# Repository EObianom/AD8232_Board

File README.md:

# AD8232_Board
AD8232 Mini ECG Breakout Board

A compact, production-ready ECG front-end built around the AD8232, designed for seamless integration into wearable and embedded systems.

Small in size, deliberate in design, and ready to manufacture.

## Overview

This project implements a highly miniaturised ECG acquisition circuit with a footprint of just 25mm × 17.7mm. It is engineered for space-constrained applications where traditional breakout boards fall short. Unlike conventional AD8232 modules, this design eliminates the bulky 3.5mm audio jack, enabling direct electrode interfacing and tighter system integration. The result is a clean, flexible, and deployment-ready biosignal front-end.

## Features
- Ultra-compact PCB (25mm × 17.7mm)
- Based on the AD8232 analog front-end for ECG signal conditioning
- Direct electrode interface (no audio jack) for reduced size and flexibility
- Carefully designed layout for low-noise signal acquisition
- Manufacturing-ready with full fabrication and assembly files

## Repository Contents
This repository provides a complete, production-ready hardware package:
1. Schematic
2. PCB Layout: Optimised layout focused on compactness.
3. Footprints: All components mapped to manufacturable, assembly-ready footprints.
4. Gerber Files: Fabrication files ready for immediate PCB manufacturing.
5. BOM (JLC Format): Bill of Materials.
6. CPL File: Pick-and-place file for automated component assembly.

## Getting Started

1. Review the schematic to understand the circuit design
2. Open the PCB layout in KiCad to inspect routing and placement
3. Use the Gerber files to order your PCB
4. Upload the BOM and CPL files to JLCPCB (or similar) for assembly

Once assembled, the board can be interfaced with a microcontroller ADC for signal capture and processing.

## Applications

- Wearable health monitoring devices
- Embedded ECG systems
- Biomedical research prototypes
- Low-power biosignal acquisition platforms

---

Disclaimer
This design is intended for research and development purposes only. It is not certified for medical or clinical use. This work is licensed under a Creative Commons Attribution-NonCommercial 4.0 International License.

Contributions and improvements are welcome.
Feel free to open an issue or submit a pull request.

Designed and developed by Ekenedirichukwu Obianom.

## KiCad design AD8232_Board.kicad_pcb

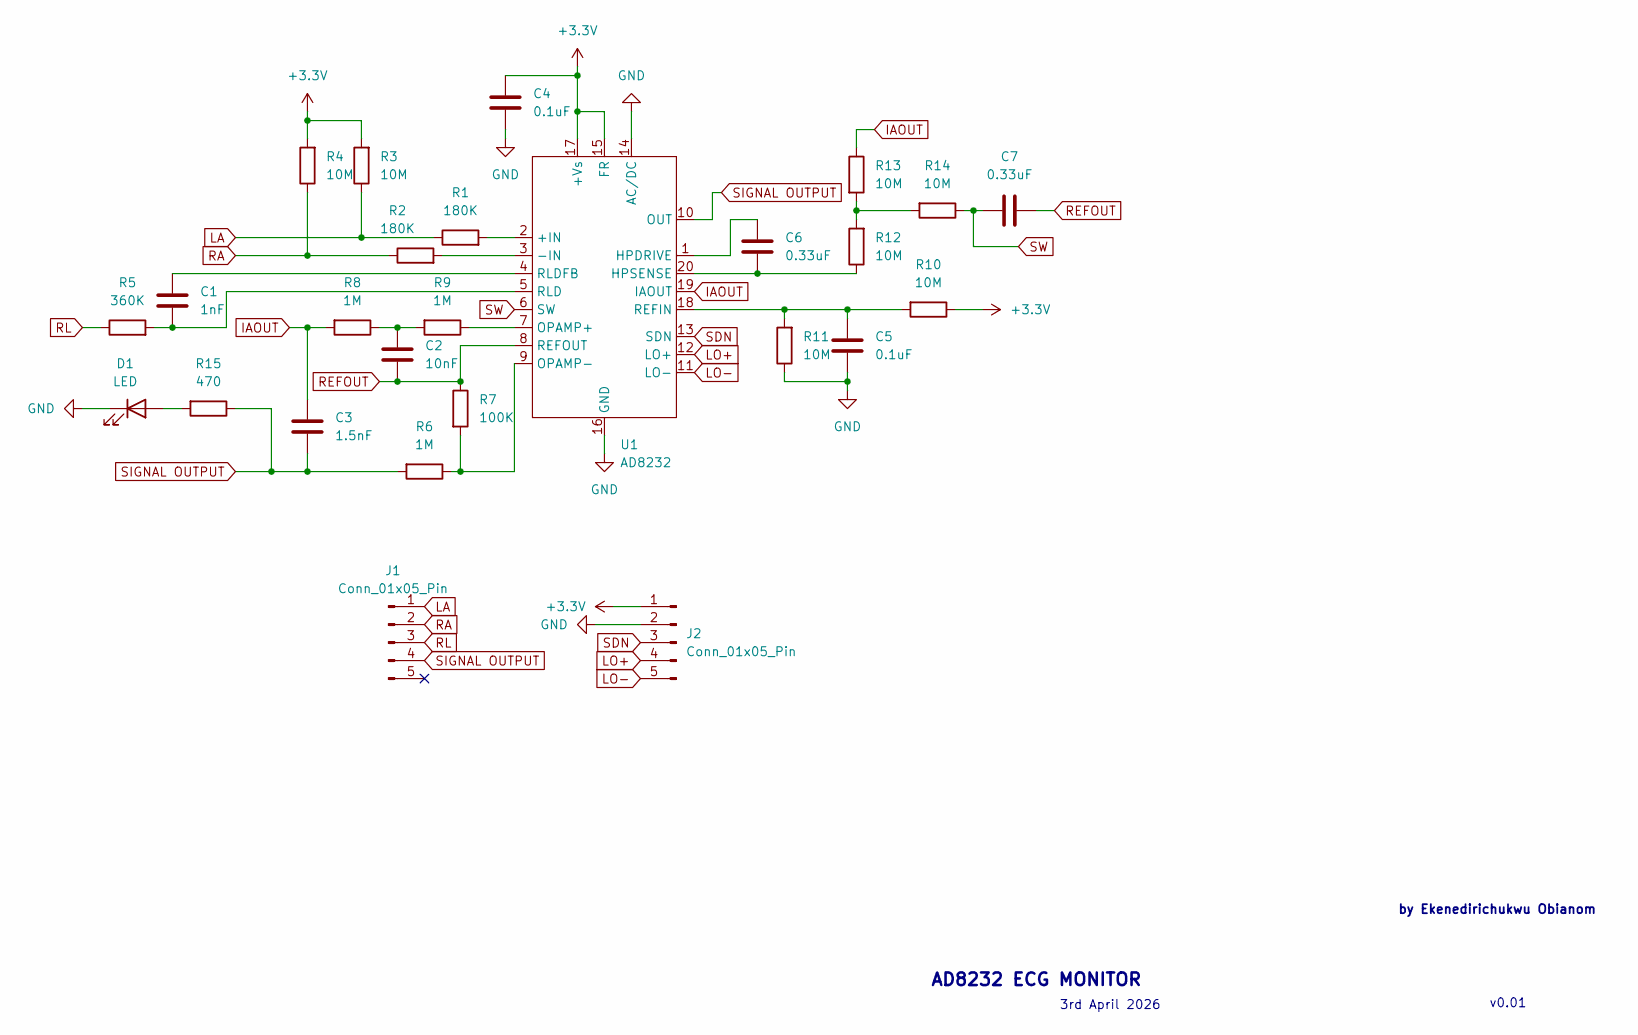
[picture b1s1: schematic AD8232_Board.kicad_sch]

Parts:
C1: 1nF; C_0603_1608Metric
C2: 10nF; C_0603_1608Metric
C3: 1.5nF; C_0603_1608Metric
C4, C5: 0.1uF; C_0603_1608Metric
C6, C7: 0.33uF; C_0603_1608Metric
D1: LED; LED_0603_1608Metric
J1, J2: Conn_01x05_Pin; PinHeader_1x05_P2.54mm_Vertical
R1, R2: 180K; R_0805_2012Metric
R3, R4, R10, R11, R12, R13, R14: 10M; R_0603_1608Metric
R5: 360K; R_1206_3216Metric
R6, R8, R9: 1M; R_0805_2012Metric
R7: 100K; R_0603_1608Metric
R15: 470; R_0805_2012Metric
U1: AD8232; QFN-20-1EP_4x4mm_P0.5mm_EP2.6x2.6mm

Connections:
+3.3V: C4.1, J2.1, R3.2, R4.2, R10.1, U1.15 (FR), U1.17 (+Vs)
GND: C4.2, C5.2, D1.1 (K), J2.2, R11.1, U1.14 (AC/DC), U1.16 (GND), U1.21 (GND)
IAOUT: C3.1, R8.2, R13.1, U1.19 (IAOUT)
LA: J1.1, R1.1, R3.1
LO+: J2.4, U1.12 (LO+)
LO-: J2.5, U1.11 (LO-)
unnamed: C2.1, R8.1, R9.2
unnamed: D1.2 (A), R15.2
unnamed: R12.2, R13.2, R14.2
unnamed: R1.2, U1.2 (+IN)
unnamed: R2.2, U1.3 (-IN)
unnamed: C6.1, U1.1 (HPDRIVE)
unnamed: C6.2, R12.1, U1.20 (HPSENSE)
unnamed: R9.1, U1.7 (OPAMP+)
unnamed: R6.1, R7.2, U1.9 (OPAMP-)
unnamed: C5.1, R10.2, R11.2, U1.18 (REFIN)
unnamed: C1.2, R5.2, U1.5 (RLD)
unnamed: C1.1, U1.4 (RLDFB)
RA: J1.2, R2.1, R4.1
REFOUT: C2.2, C7.2, R7.1, U1.8 (REFOUT)
RL: J1.3, R5.1
SDN: J2.3, U1.13 (SDN)
SIGNAL OUTPUT: C3.2, J1.4, R6.2, R15.1, U1.10 (OUT)
SW: C7.1, R14.1, U1.6 (SW)

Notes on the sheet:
by Ekenedirichukwu Obianom
3rd April 2026
v0.01
AD8232 ECG MONITOR

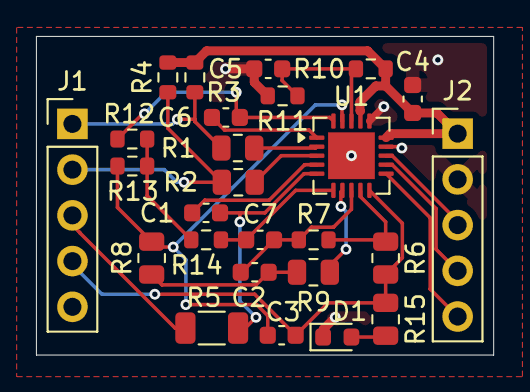
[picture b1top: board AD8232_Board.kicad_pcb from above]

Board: 4 copper layers, 25.4 x 17.7 mm, 26 parts (0 on the bottom side), 24 nets.

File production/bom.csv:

Designator,Footprint,Quantity,Value,LCSC Part #
C1,0603,1,1nF,
C2,0603,1,10nF,
C3,0603,1,1.5nF,
"C4, C5",0603,2,0.1uF,
"C6, C7",0603,2,0.33uF,
D1,0603,1,LED,
"J1, J2",PinHeader_1x05_P2.54mm_Vertical,2,Conn_01x05_Pin,
"R1, R2",0805,2,180K,
"R10, R11, R12, R13, R14, R3, R4",0603,7,10M,
R15,0805,1,470,
R5,1206,1,360K,
"R6, R8, R9",0805,3,1M,
R7,0603,1,100K,
U1,QFN-20-1EP_4x4mm_P0.5mm_EP2.6x2.6mm,1,AD8232,

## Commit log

2026-04-03 AD8232 Symbol added
2026-04-03 Library and Schematic Update
    - Updated the AD8232 Symbol to include 21 pins with the 21st auto connected to ground.
    - Completed the schematic for the board and attached footprints to them.
2026-04-03 Changed the footprint for AD8232
2026-04-03 PCB designed and Gerber files generated
2026-04-03 light update to last commitment
    jclpcb bom and cpl included
2026-04-03 Enhance README with detailed project informatio
    Expanded the README to provide detailed information about the AD8232 Mini ECG Breakout Board, including features, repository contents, design notes, getting started instructions, applications, licens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
2026-04-08 Add image to README for visual representation
    Added an image to the README for visual representation.
2026-04-08 Add image to README for better visualization
    Added an image to enhance the README content.
2026-04-08 Update silkscreen and soldermask settings
    Add multiple bottom silkscreen text labels (RL, AN, NC, LA, RA, 3.3, GND, SDN, LO+, LO-) to AD8232_Board.kicad_pcb and remove an explicit solder_mask_min_width entry. Adjust solder mask to copper cle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
2026-04-08 Create LICENSE
2026-04-09 Add production BOM, designators, and positions
    Remove .gitignore rules that excluded exported BOM files (*.xml, *.csv) so production artifacts can be tracked. Add production/bom.csv (component list with quantities and LCSC part references), produ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
